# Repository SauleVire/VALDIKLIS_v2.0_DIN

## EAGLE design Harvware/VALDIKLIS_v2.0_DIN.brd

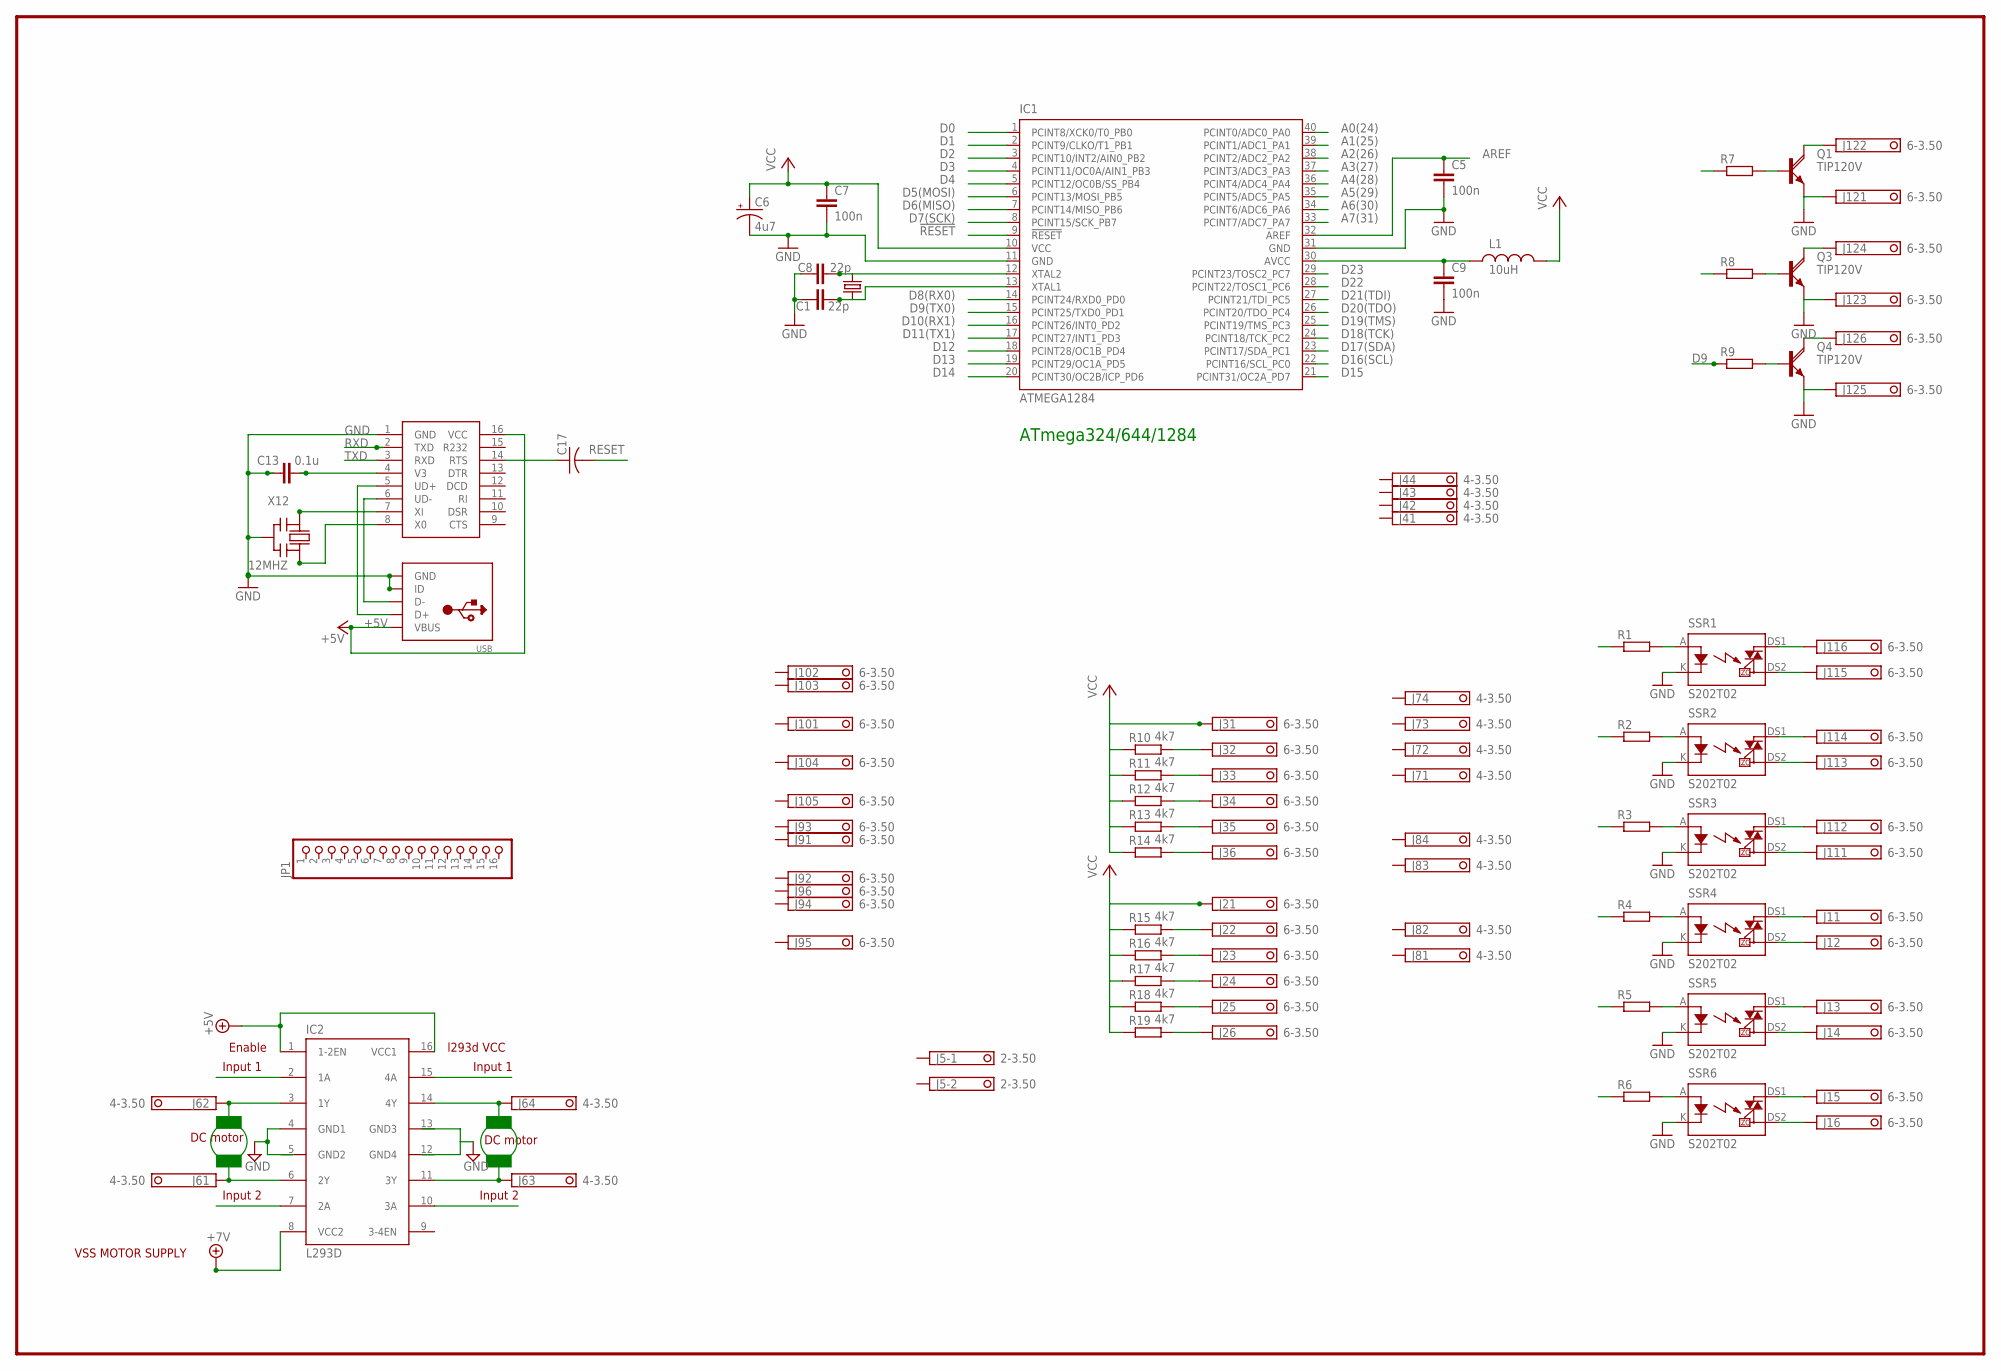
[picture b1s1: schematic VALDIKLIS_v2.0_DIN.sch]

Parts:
C1, C8: 22p; C025-024X044
C5, C7, C9: 100n; CAP-PTH-SMALL
C6: 4u7; CPOL-RADIAL-10UF-25V
C13: 0.1u; C0805
C17: C-USC0805K; C0805K
IC1: ATMEGA1284; DIL40
IC2: L293D; DIL16
J1, J2, J3, J9, J10, J11, J12: 6-3.50
J4, J6, J7, J8: 4-3.50
J5: 2-3.50
JP1: PINHD-1X16; 1X16
L1: 10uH; RES-AXIAL-0.4
Q1, Q3, Q4: TIP120V; TO220AV
R1, R2, R3, R4, R5, R6, R7, R8, R9: R-EU_0309/V; 0309V
R10, R11, R12, R13, R14, R15, R16, R17, R18, R19: 4k7; 0309V
SSR1, SSR2, SSR3, SSR4, SSR5, SSR6: S202T02
U$10: CH340G; SO016
USB: USBMOLEX; USB-MINIB-THM-MOLEX
X2: 16MHz; HC49US
X12: 12MHZ; CERM_OSC

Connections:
!RESET: IC1.9 (!RESET)
+5V: IC2.1 (1-2EN), IC2.16 (VCC1), U$10.16 (VCC), USB.VBUS
+7V: IC2.8 (VCC2)
A0(24): IC1.40 (PCINT0/ADC0_PA0)
A1(25): IC1.39 (PCINT1/ADC1_PA1)
A2(26): IC1.38 (PCINT2/ADC2_PA2)
A3(27): IC1.37 (PCINT3/ADC3_PA3)
A4(28): IC1.36 (PCINT4/ADC4_PA4)
A5(29): IC1.35 (PCINT5/ADC5_PA5)
A6(30): IC1.34 (PCINT6/ADC6_PA6)
A7(31): IC1.33 (PCINT7/ADC7_PA7)
AREF: C5.1, IC1.32 (AREF)
AVCC: C9.1, IC1.30 (AVCC), L1.P$1 (1)
D0: IC1.1 (PCINT8/XCK0/T0_PB0)
D1: IC1.2 (PCINT9/CLKO/T1_PB1)
D2: IC1.3 (PCINT10/INT2/AIN0_PB2)
D3: IC1.4 (PCINT11/OC0A/AIN1_PB3)
D4: IC1.5 (PCINT12/OC0B/SS_PB4)
D5(MOSI): IC1.6 (PCINT13/MOSI_PB5)
D6(MISO): IC1.7 (PCINT14/MISO_PB6)
D7(SCK): IC1.8 (PCINT15/SCK_PB7)
D8(RX0): IC1.14 (PCINT24/RXD0_PD0)
D9: R9.1
D9(TX0): IC1.15 (PCINT25/TXD0_PD1)
D10(RX1): IC1.16 (PCINT26/INT0_PD2)
D11(TX1): IC1.17 (PCINT27/INT1_PD3)
D12: IC1.18 (PCINT28/OC1B_PD4)
D13: IC1.19 (PCINT29/OC1A_PD5)
D14: IC1.20 (PCINT30/OC2B/ICP_PD6)
D15: IC1.21 (PCINT31/OC2A_PD7)
D16(SCL): IC1.22 (PCINT16/SCL_PC0)
D17(SDA): IC1.23 (PCINT17/SDA_PC1)
D18(TCK): IC1.24 (PCINT18/TCK_PC2)
D19(TMS): IC1.25 (PCINT19/TMS_PC3)
D20(TDO): IC1.26 (PCINT20/TDO_PC4)
D21(TDI): IC1.27 (PCINT21/TDI_PC5)
D22: IC1.28 (PCINT22/TOSC1_PC6)
D23: IC1.29 (PCINT23/TOSC2_PC7)
GND: C1.1, C5.2, C6.2 (-), C7.2, C8.1, C9.2, C13.1, IC1.11 (GND), IC1.31 (GND), IC2.4 (GND1), J12.1, J12.3, J12.5, Q1.E, Q3.E, Q4.E, SSR1.K, SSR2.K, SSR3.K, SSR4.K, SSR5.K, SSR6.K, U$10.1 (GND), USB.GND, USB.ID, X12.P$2 (GND)
GND2: IC2.5 (GND2)
GND3: IC2.13 (GND3)
GND4: IC2.12 (GND4)
unnamed: IC2.14 (4Y), J6.4
unnamed: J11.5, SSR1.DS2
unnamed: Q1.B, R7.2
unnamed: J11.6, SSR1.DS1
unnamed: J11.4, SSR2.DS1
unnamed: U$10.6 (UD-), USB.D-
unnamed: U$10.7 (XI), X12.P$1 (IN)
unnamed: Q3.B, R8.2
unnamed: Q4.B, R9.2
unnamed: U$10.5 (UD+), USB.D+
unnamed: R1.2, SSR1.A
unnamed: J11.3, SSR2.DS2
unnamed: R2.2, SSR2.A
unnamed: J11.2, SSR3.DS1
unnamed: J11.1, SSR3.DS2
unnamed: J1.6, SSR6.DS2
unnamed: J1.5, SSR6.DS1
unnamed: J1.4, SSR5.DS2
unnamed: J1.3, SSR5.DS1
unnamed: J1.2, SSR4.DS2
unnamed: J1.1, SSR4.DS1
unnamed: R3.2, SSR3.A
unnamed: R4.2, SSR4.A
unnamed: R5.2, SSR5.A
unnamed: U$10.8 (X0), X12.P$3 (OUT)
unnamed: R6.2, SSR6.A
unnamed: C13.2, U$10.4 (V3)
unnamed: J3.5, R13.2
unnamed: C17.1, U$10.14 (RTS)
unnamed: J3.3, R11.2
unnamed: J3.4, R12.2
unnamed: J3.2, R10.2
unnamed: J3.6, R14.2
unnamed: J2.3, R16.2
unnamed: J2.4, R17.2
unnamed: J2.2, R15.2
unnamed: J2.5, R18.2
unnamed: J2.6, R19.2
unnamed: J12.4, Q3.C
unnamed: J12.6, Q4.C
unnamed: J12.2, Q1.C
unnamed: C1.2, IC1.13 (XTAL1), X2.1
unnamed: C8.2, IC1.12 (XTAL2), X2.2
unnamed: IC2.3 (1Y), J6.2
unnamed: IC2.6 (2Y), J6.1
RESET: C17.2
RXD: U$10.2 (TXD)
TXD: U$10.3 (RXD)
VCC: C6.1 (+), C7.1, IC1.10 (VCC), J2.1, J3.1, L1.P$2 (2), R10.1, R11.1, R12.1, R13.1, R14.1, R15.1, R16.1, R17.1, R18.1, R19.1

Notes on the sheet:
ATmega324/644/1284
DC motor
Input 1
Input 2
Enable
l293d VCC
VSS MOTOR SUPPLY

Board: 2 copper layers, 56 parts (0 on the bottom side), 50 nets, no tracks yet.

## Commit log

2016-01-30 :confetti_ball: Added .gitattributes & .gitignore files
2016-01-31 Darbo pradžia
2016-01-31 pradžia 2
2016-02-03 tesinys
2016-02-14 eiga
2016-02-17 maketas 1284
2016-02-17 bootloader MightyCore
    tested bootloader 20MHz https://github.com/MCUdude/MightyCore/
2016-02-22 Irškojimai-sprendimai
    Relės pakeistos l293 mikroschema skirta variklių valdymui.

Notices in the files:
parts and their libraries:
dframes_1: Copyright (C) 2004, Bob Starr (bobstarr@mindspring.com)
